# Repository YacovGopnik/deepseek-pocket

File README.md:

# DeepSeek в кармане

Самодельный карманный гаджет на ESP32-C3. Умеет:
- чат с DeepSeek;
- инженерный калькулятор с графиками и решением уравнений;
- справочник, конспекты, игры;
- общую «Комнату» для владельцев таких же устройств;
- игры вдвоём по радио;
- галерею на SD-карте;
- вывод картинок и экрана с компьютера;
- управление с телефона.

Обновляется по воздуху с этого репозитория.

## Что нужно

- ESP32-C3 Super Mini
- дисплей ST7789 240×240 1,3" (без вывода CS)
- аналоговый джойстик KY-023
- по желанию:
  - LiPo-аккумулятор и модуль зарядки с повышением до 5 В (USB-C), выключатель;
  - модуль microSD (например, V717) с конденсатором 100 мкФ;
  - пищалка, ИК-светодиод, белый светодиод (без SD-карты).

## Подключение

| Дисплей | ESP32-C3 |   | Джойстик | ESP32-C3 |
|---------|----------|---|----------|----------|
| SCL     | GPIO4    |   | VRx      | GPIO0    |
| SDA     | GPIO6    |   | VRy      | GPIO1    |
| DC      | GPIO5    |   | SW       | GPIO7    |
| RES     | GPIO21 (или GPIO3, см. ниже) | | +5V | **3V3** |
| BLK     | GPIO10   |   | GND      | GND      |
| VCC     | 3V3      |   |          |          |
| GND     | GND      |   |          |          |

### ESP32-S3 (S3-Zero)

Прошивка сама подставляет распиновку под плату: в Arduino IDE выберите **ESP32S3 Dev Module**, USB CDC On Boot: Enabled, Flash Size: 4MB, PSRAM: QSPI PSRAM, Partition Scheme: Minimal SPIFFS. По воздуху гаджет на S3 сам берёт сборки для S3 (`firmware-s3*.bin`).

| Что | S3-Zero |
|---|---|
| Экран SCL, SDA, DC, RES, BLK | 12, 11, 10, 9, 8 (VCC — 3V3) |
| Джойстик VRx, VRy, SW | 1, 2, 7 (питание — 3V3) |
| SD-карта SCK, MOSI, MISO, CS | 5, 6, 13, 4 (VCC — 5V; у карты своя шина SPI, подтяжки не нужны) |
| Батарея (делитель 100к + 100к) | 3 |
| Пищалка / ИК-светодиод | RX (44) / TX (43) |
| Усилитель MAX98357A: BCLK, LRC, DIN | 14, 15, 16 (VIN — 5V, SD и GAIN не подключать) |
| Микрофон INMP441: SCK, WS, SD | 14, 15, 17 (VDD — 3V3, L/R — GND) |
| Датчик наклона ADXL345: SDA, SCL | 38, 39 (VCC — 3V3, CS — 3V3, SDO — GND); Настройки → Наклон: уровень, калибровка, управление в играх |
| Фонарик / вибромотор | 18 / 40 |
| Не трогать | 0 (кнопка BOOT), 19–20 (USB), 21 (светодиод на плате), 45 (влияет на запуск) |

Выводы 14–18 и 38–40 у S3-Zero — площадки на плате. В нашем гаджете они выведены проводами на отдельную гребёнку. Порядок, если смотреть с гребёнкой вверх: **40, 39, 38, 18, 17, 14, 15, 16**.

### Сенсорные кнопки S3

В Настройки → Сенсорные кнопки доступны режимы 4 направления и 6 кнопок + BOOT. В режиме шести кнопок GPIO4/5/6/13 — вверх/вниз/влево/вправо, GPIO14 — OK, GPIO7 — ESC. Физический OK — кнопка BOOT платы. Перед включением режима отсоедините провод SW джойстика от GPIO7 и оборудование I²S от GPIO14. Цифровой звук I²S в этом режиме отключён. Для SD-карты необходимо выключить сенсорное управление. Режим меняется с перезапуском. На главном экране удерживайте BOOT, затем отпустите. В диалоге короткое нажатие BOOT включает режим «Только сенсоры» (аналоговые оси игнорируются), долгое выключает сенсоры. Не удерживайте BOOT при подаче питания или аппаратном сбросе.

### Батарея

- **RES экрана** можно подключить к GPIO21 (TX) или к GPIO3: прошивка подаёт сброс на оба вывода и сама понимает схему.
- **Проценты заряда.** RES подключите на GPIO21. Нужны два резистора по 100 кОм: один от «+» питания к GPIO3, второй от GPIO3 к GND. Прошивка сама находит делитель при включении.

### Выводы, которые делят SD-карта и дополнительные детали

GPIO2, GPIO8, GPIO9 и GPIO20 нужны либо SD-карте, либо пищалке, ИК-пульту и фонарику:

| Вывод | С SD-картой | Без SD-карты |
|---|---|---|
| GPIO8 | SCK карты | ИК-светодиод (через транзистор) |
| GPIO2 | MOSI карты | фонарик (через транзистор) |
| GPIO20 | MISO карты | пищалка |
| GPIO9 | CS карты | — |

Когда включена SD-карта, прошивка не трогает пищалку, ИК и фонарик. При попытке их включить она говорит, что вывод занят картой.

## Сборка в Arduino IDE

Проводом прошивать нужно один раз, дальше обновления приходят по воздуху.

1. На GitHub: **Code → Download ZIP**. Распакуйте архив («Извлечь всё»), не открывайте файлы прямо из ZIP.
2. Скетч лежит в папке **`deepseek_c3`**: откройте `deepseek_c3/deepseek_c3.ino`. В Arduino IDE должны появиться вкладки с остальными файлами (`admin.h`, `calc.h`...).
3. Пакет плат **esp32** (Espressif) 3.x. Библиотеки (Скетч → Подключить библиотеку → Управлять библиотеками):
   - **Adafruit ST7735 and ST7789**, **Adafruit GFX**, **ArduinoJson** (7.x), **TJpg_Decoder** (Bodmer);
   - для сборки с Bluetooth ещё **NimBLE-Arduino 1.4.3**.
4. Инструменты:
   - Плата **ESP32C3 Dev Module** с разметкой **Partition Scheme: Minimal SPIFFS (1.9MB APP with OTA/190KB SPIFFS)**.

     Другой вариант: плата **Nologo ESP32C3 Super Mini** с разметкой **Huge APP**. Так прошивка выйдет на 16 КБ меньше, и именно так собирает GitHub. Настоящую разметку в обоих случаях задаёт файл `partitions.csv` в папке скетча.
   - **USB CDC On Boot: Enabled** — обязательно. Иначе вывод в монитор порта идёт через GPIO21 и сбрасывает экран.
   - **Erase All Flash Before Sketch Upload: Disabled** — иначе каждая прошивка стирает сеть, ключ и файлы.
5. Загрузить. Версия, собранная в Arduino IDE, показывается как «1». Номера сборок с GitHub больше, поэтому гаджет предложит обновиться.

Если плата не появляется в списке портов: зажмите кнопку **BOOT**, подключите USB и отпустите кнопку. Загрузите прошивку, затем нажмите **RST**.

## Первый запуск

Гаджет создаёт сеть Wi-Fi **DeepSeek-Setup**. Подключитесь к ней с телефона: откроется страница, где вводятся сеть Wi-Fi и ключ DeepSeek (получить его можно на platform.deepseek.com). Ключи и пароли хранятся только в памяти платы, в файлах прошивки их нет.

## Главный экран

После включения открывается главный экран, как у телефона:
- **Сверху** строка состояния: время, Wi-Fi, заряд, новые сообщения комнаты.
- **Ниже** иконки приложений 3×3 на нескольких страницах.

Ручкой выбирается иконка. Если упереться в край, открывается соседняя страница. Нажатие открывает приложение, удержание кнопки возвращает назад.

Приложения: DeepSeek, Комната, Игры, Калькулятор, Справочник, Конспекты, Сохранено, Википедия, Картинки, Галерея, Погода, Курсы, Часы, Таймер, Секундомер, Пульт (ИК), Bluetooth, Экран ПК, Телефон, Настройки, Админ.

**Если гаджет завис** — держите кнопку джойстика 6 секунд: он перезапустится и откроет главный экран. Это срабатывает, даже если программа намертво застряла (например, на SD-карте). Через 2 секунды экран гаснет, держите дальше.

Что настраивается:
- **Ось Y джойстика** — если вверх и вниз на ручке перепутаны.
- **Поворот экрана** — поворачивает картинку на 90° за нажатие, например чтобы держать гаджет боком. Ручка поворачивается вместе с картинкой.
- **Джойстик** — чувствительность: 1 — отклонять до упора, 5 — хватает лёгкого наклона.

## Возможности

- **Чат с DeepSeek.** Помнит переписку, ответ печатается по мере генерации. Есть «решить по шагам» и «объяснить проще». Удержание кнопки на клавиатуре чата открывает меню: новый чат, шаблоны вопросов, сохранённое.
- **Языки:** русский, английский, китайский. Экранная клавиатура с подсказками слов.
- **Тексты без интернета:** шаблоны вопросов, сохранённые ответы и конспекты.
- **Справочник:** формулы, константы, таблица Менделеева.
- **Калькулятор** с переменной x, графиками и уравнениями (см. ниже).
- **Интернет:** Википедия, картинки (Wikimedia Commons), погода, курсы ЦБ.
- **Время:** часы, таймер, секундомер.
- **Галерея:** картинки с телефона, с компьютера или из поиска. Без SD-карты хранится до 30 штук, с картой до 99.
- **Игры:**
  - шахматы против DeepSeek или самой платы;
  - «Подземелье 3D» — стрелялка от первого лица: ручка — идти и поворачивать, кнопка — выстрел;
  - «Песочница» — двумерный мир из блоков: копать, строить, мастерить кирки и мечи, ночью отбиваться от слизней; цель — золотая корона (см. ниже);
  - «Гонки», «Райдер», «Блоки», 2048, «Змейка», «Падающие блоки», «Лабиринт», «Память», «Пинг-понг», «Летящая птичка», «Арканоид», «Пришельцы», «Сапёр», «Повтори»;
  - «Куб-раннер» — уровень с финишем, шипами и платформами. Короткое нажатие кнопки или наклон джойстика вверх запускает забег, прыжок и повтор попытки. Удержание кнопки возвращает в меню. Прогресс и рекорд показываются в процентах.
  - игры с DeepSeek: «Викторина», «Приключение», «Угадай, кто я»;
  - общая таблица рекордов;
  - крестики-нолики через комнату и «Крестики рядом» по радио.
- **Пульт (ИК)** — пульты из базы Flipper-IRDB. Скачиваются с GitHub прямо с гаджета или загружаются файлом .ir с телефона. Только без SD-карты. Схема: GPIO8 → база NPN-транзистора (S9014), коллектор → 5V, эмиттер → «+» ИК-светодиода, «−» светодиода → резистор 33–68 Ом → GND.
- **Фонарик:** Настройки → Фонарик. Белый светодиод на GPIO2 через транзистор, схема в начале скетча рядом с `PIN_LED`. Только без SD-карты.
- **Пищалка** на GPIO20. Для активной пищалки в скетче поставьте `BUZZER_ACTIVE = true`. Звук настраивается: нет / сигналы / всё.
- **Wi-Fi и экран:** до 5 сетей Wi-Fi, автогашение экрана, заставка с часами.

## Телефон как пульт и клавиатура (Wi-Fi)

Приложение **«Телефон»** показывает адрес гаджета, например `http://192.168.1.35`. Подключите телефон к той же сети Wi-Fi и откройте этот адрес в любом браузере (Android или iPhone). Ничего устанавливать не нужно: гаджет сам отдаёт страницу.

На странице:
- **Стрелки.** Пока стрелку держат, это как наклон ручки.
- **OK.** Это как нажатие ручки. Если держать дольше полсекунды, получится долгое нажатие.
- **Поле для текста** с кнопками «Отправить» (вставить и нажать OK) и «Только вставить».

Пульт работает везде, где есть Wi-Fi: в играх, меню и при вводе текста. Из приложения «Телефон» можно выйти. Если связь пропала, нажатые кнопки отпускаются сами. Пульт есть только в полной сборке.

## Экран ПК (USB)

Приложение **«Экран ПК»** показывает на гаджете картинки и экран компьютера по USB-кабелю. На компьютере откройте в Chrome или Edge страницу [yacovgopnik.github.io/deepseek-pocket/pc.html](https://yacovgopnik.github.io/deepseek-pocket/pc.html), нажмите «Подключить» и выберите порт гаджета. Для передачи с ПК выберите «ПК → гаджет» в меню приложения. Монитор порта в Arduino IDE при этом должен быть закрыт.

- **Картинка.** Перетащите файл или вставьте через Ctrl+V, затем «Показать на гаджете» или «Сохранить в галерею».
- **Трансляция экрана.** Гаджет показывает выбранное окно, вкладку или весь экран, от 2 до 20 кадров в секунду.

- **Экран гаджета на ПК.** Выберите «Гаджет → ПК» на гаджете, вернитесь в меню и нажмите «Экран гаджета» на странице. Можно увеличивать изображение, открывать его на весь экран и сохранять PNG. На S3 изображение 240×240, на C3 — 120×120 для экономии памяти. Для остановки на гаджете снова откройте «Экран ПК» и выберите остановку трансляции. Доступно в полной сборке.

Как устроен обмен: страница сжимает кадр в JPEG 240×240 и передаёт его кусками по 2 КБ, гаджет подтверждает каждый кусок. Все подробности протокола — в начале раздела «ЭКРАН ПК» в скетче.

## Игры вдвоём рядом (без интернета)

**Игры → Крестики рядом** — два гаджета связываются напрямую по радио (ESP-NOW), без роутера и интернета, на расстоянии примерно до 100 м. На время игры Wi-Fi отключается от сети, а после игры подключается снова.

## SD-карта

| SD-модуль | ESP32-C3 |
|---|---|
| SCK | GPIO8 |
| MOSI | GPIO2 |
| MISO | GPIO20 |
| CS | GPIO9 |
| VCC | **5V** (у модуля свой стабилизатор 3,3 В; от 3V3 ему не хватает) |
| GND | GND, отдельным проводом к плате |

- **Конденсатор 100 мкФ** (можно вместе с керамическим 0,1 мкФ) ставится прямо на выводы VCC–GND модуля. Без него карта отвечает через раз: в момент обращения к ней проседает питание.
- **Два резистора по 10 кОм:** от GPIO2 к 3V3 и от GPIO9 к 3V3. При включении эти выводы должны быть в высоком уровне, иначе плата не загрузится.
- **Карта** до 32 ГБ, формат FAT32.

Включение: **Настройки → SD-карта**, гаджет перезапустится. Состояние видно там же: «работает», «не найдена» или «сбой N». После включения:
- галерея хранится на карте (папка `pics/`, до 99 картинок);
- в меню **Настройки → Обновление** появляется пункт **«Сборки на SD-карте»**: скачать обе сборки на карту (папка `fw/`) и переключаться между ними без интернета.

Заметки, сохранённые ответы и настройки остаются во внутренней памяти.

Если сразу после включения карта не отвечает, гаджет пробует снова каждые 15 секунд в течение 2 минут.

**Защита от зависания.** Если запуск с картой не дошёл до конца, на следующем запуске карта выключается сама, а на заставке видно, на каком шаге всё остановилось. Удержание кнопки при включении тоже выключает карту.

**Как устроено.** Шина SPI у платы одна, а у экрана нет вывода CS. Поэтому на время работы с картой выводы шины переключаются на неё, а потом обратно на экран. При переключении линия такта не дёргается: иначе экран без CS сбивается и перестаёт понимать команды.

**Проверка.** В папке [`tests`](tests) лежат отдельные скетчи:
- `sd_diag` проверяет карту медленно, быстро и вместе с экраном и пишет, в чём беда: питание и провода, длинные провода или прошивка;
- `sd_screen_test` по кругу переключается между картой и экраном.

## Песочница

**Игры → Песочница.** Мир 256×96 блоков создаётся заново для каждой новой игры: холмы, деревья, пещеры, уголь, железо, золото у самого дна. День длится 5 минут, ночь 3 минуты. Под землёй темно, и нужны факелы.

- **Управление.**
  - Ручка влево/вправо — идти, вверх — прыжок. Куда наклонена ручка, туда и цель (белая рамка).
  - Нажатие — ударить по блоку, поставить выбранный блок в пустое место или ударить слизня.
  - Удержание кнопки — меню: что ставить, мастерить, сохранить и выйти.
- **Инструменты** работают сами, пока лежат в рюкзаке: самая лучшая кирка копает, самый лучший меч бьёт. Без кирки копаются только земля, песок и дерево. Деревянная кирка берёт камень и уголь, каменная — железо, железная — золото.
- **Рецепты:**
  - доски — из брёвен;
  - верстак — из досок;
  - факелы — из угля или слизи с досками;
  - у верстака: кирки, мечи, кирпич и золотая корона.
- **Сохранение.** Мир весит около 25 КБ и хранится на SD-карте, а без неё — во внутренней памяти. Он сохраняется сам каждые 3 минуты, а также через меню «Сохранить и выйти».

## Три сборки: полная, с Bluetooth и игровая

Bluetooth весит около 250 КБ, и всё вместе в память на 4 МБ не помещается. Поэтому GitHub собирает три прошивки:

- **Полная сборка** (`firmware.bin`): всё, кроме Bluetooth.
- **Сборка с Bluetooth** (`firmware-ble.bin`): связь с телефоном по Bluetooth и пульт для музыки на телефоне. В ней **нет**:
  - картинок из интернета (галерея остаётся);
  - шахмат;
  - «Подземелья 3D» и «Гонок»;
  - «Райдера», «Викторины», «Приключения»;
  - ИК-пульта и фонарика;
  - пульта с телефона по Wi-Fi;
  - «Песочницы».
- **Игровая сборка** (`firmware-games.bin`): только игры (в том числе большие), «Комната», пульт с телефона и настройки. Здесь остаётся больше места под новые большие игры. Чата DeepSeek, справочника, калькулятора и остальных приложений в ней нет. Игры с DeepSeek работают, если задан ключ.

Переключение: **Настройки → Обновление → Сменить сборку** или **Сборки на SD-карте** (туда скачиваются все три). Настройки, сети и файлы сохраняются. Для сборки в Arduino IDE поставьте в начале скетча `#define ENABLE_BLE 1` (с Bluetooth) или `#define GAMES_EDITION 1` (игровая).

В сборке с Bluetooth включите **Настройки → Bluetooth**. Гаджет называется **DS-<метка>**.

- **Телефон как клавиатура и уведомления.**
  - Откройте в Chrome на Android страницу [yacovgopnik.github.io/deepseek-pocket/ble.html](https://yacovgopnik.github.io/deepseek-pocket/ble.html) и нажмите «Подключить». Подойдёт и приложение Serial Bluetooth Terminal в режиме Bluetooth LE.
  - Текст попадает в открытое поле ввода, например как вопрос DeepSeek. Если поле ввода не открыто, текст всплывает как уведомление.
  - Строка с `N:` в начале — всегда уведомление, с `T:` — только вставить.
- **Пульт для телефона.** На телефоне в настройках Bluetooth подключитесь к **DS-<метка>**. На гаджете откройте приложение Bluetooth → Пульт. Ручка влево и вправо переключает трек, вверх и вниз меняет громкость, нажатие ставит на паузу.

Wi-Fi и Bluetooth делят память. Если запросы в интернет начнут срываться, выключите Bluetooth.

## Страницы для телефона и компьютера

Страницы `ble.html` и `pc.html` лежат в корне репозитория. Их адреса `yacovgopnik.github.io/...` работают, когда в репозитории включён GitHub Pages: **Settings → Pages → Branch: main, папка / (root)**. Страница `room.html` открывает «Комнату» в браузере.

## Администратор

Один человек может быть администратором всех гаджетов с этой прошивкой. Команды подписываются ключом, который получается из логина и пароля админа (ECDSA P-256). В прошивке хранится только открытый ключ `ADMIN_PUBKEY`, по которому гаджеты проверяют подпись. Подделать команду без пароля нельзя, даже зная исходный код. Пароль нигде не записывается.

Как стать админом:

1. **Настройки → Администратор → Создать ключ**: ввести логин и пароль. Открытый ключ появится на экране и в мониторе порта (115200).
2. Вписать его в `ADMIN_PUBKEY` в начале скетча и выпустить новую версию.
3. **Настройки → Администратор → Войти** с теми же логином и паролем. Вход действует до перезапуска. На главном экране появляется приложение «Админ».

Что может админ:

- **Гаджеты на связи**: имя, комната, версия прошивки, заряд. Для каждого гаджета: обновить прошивку, перезапустить, выгнать из комнаты, заблокировать.
- **Объявление всем**: всплывает на экране всех гаджетов, в том числе тех, кто подключится позже.
- **Сообщения комнаты**: удалить сообщение у всех, заблокировать автора. Заблокированный не может писать, а его сообщения у других не показываются.
- **Закрепить в комнате**: строка сверху экрана комнаты.
- **Обновить все гаджеты / перезапустить все**.

Владелец гаджета видит каждое действие админа. Обновление и перезапуск начинаются через 10 секунд, и их можно отменить кнопкой.

Команды идут через тот же открытый сервер, что и «Комната». Поэтому их получают только гаджеты, у которых в комнате задано имя и включены «Сообщения в фоне». Старые и повторённые команды не принимаются: нужно точное время, гаджет берёт его из интернета.

## Калькулятор: функции, графики, уравнения

Клавиша **2nd** переключает на вторую страницу клавиш, **1st** возвращает обратно. Переменная **x** есть на обеих страницах.

- **Функции.** Вводите выражение с x: `2x²-3x+1`, `sin(x)/x`, `√x`, `3x^4`. Неявное умножение работает (`2x`, `3(x+1)`). Результата у такого выражения нет, калькулятор пишет «функция f(x)».
- **График y(x)** (2nd → `y(x)`):
  - вверх/вниз — масштаб, влево/вправо — сдвиг;
  - нажатие — курсор со значениями x и y, удержание — назад;
  - масштаб по y подбирается сам;
  - если выражение пустое, строится последняя функция;
  - для sin/cos/tan в градусах окно по умолчанию шире (720°).
- **Уравнения** (2nd → `x=?`). Знак равенства вводится клавишей `L=R`: `x²=x+2`, `3x^4=48`. Без знака равенства считается «выражение = 0».
  - Многочлены и одночлены до 8-й степени решаются точно: рациональные корни находятся целиком, показывается кратность корней, комплексные корни выводятся как `a ± bi`.
  - Остальные уравнения (`sin(x)=0,5`, `1/x=2`, `√x=2`) решаются приближённо: ищется смена знака на отрезке. Отрезок: [-100; 100], для тригонометрии в градусах [-720; 720], в радианах [-20; 20]. Корни, в которых график лишь касается оси, так не находятся.

## Комната

Гаджеты с этой прошивкой встречаются в общей комнате `lobby` на открытом MQTT-сервере `broker.emqx.io`.

- **Сообщения** идут в теме `dspocket/v1/<комната>` в виде `метка<TAB>имя<TAB>текст`.
- **Присутствие** («кто в комнате») — в теме `<комната>/p`.
- **Аватарки 24×24** — в теме `<комната>/a/<метка>`: 576 байт, сохраняемое сообщение.
- **Ответ DeepSeek:** сообщение, начатое с `@ai`, получает ответ, который видят все.

В комнату можно зайти и из браузера через страницу `room.html`.

Сообщения **не шифруются** и не хранятся: их видят все, кто сейчас в комнате. Не пишите туда пароли и личные данные. Сервер и комнату по умолчанию можно поменять в начале скетча (`MQTT_HOST`, `ROOM_DEFAULT`).

## Обновление по воздуху

На гаджете: **Настройки → Обновление**. Там есть «Проверить в интернете», «С телефона» (загрузить файл `.bin` через страницу гаджета) и «Сборки на SD-карте». Если обновление оборвалось, остаётся старая прошивка.

Новые версии собираются сами. При каждом изменении кода GitHub Actions собирает все три сборки и кладёт в папку `firmware/`:
- `firmware/firmware.bin` — полная сборка;
- `firmware/firmware-ble.bin` — сборка с Bluetooth;
- `firmware/firmware-games.bin` — игровая сборка;
- `firmware/version.txt` — номер версии.

Гаджет сравнивает этот номер со своим и предлагает обновиться. Репозиторий задаётся строкой `OTA_REPO` в начале скетча.

Китайский язык выключен (`ENABLE_CJK 0` в начале скетча), иначе прошивка не помещается в разметку с обновлением по воздуху.

## Плата

Черновик печатной платы-основы лежит в папке [`hardware`](hardware/README.md). Он сделан до SD-карты и модуля зарядки с USB-C, поэтому будет переделан под настоящие размеры модулей.

## Шрифты

Латиница, кириллица и знаки формул сделаны из DejaVu Sans Mono, иероглифы — из GNU Unifont и Noto Sans CJK. У этих шрифтов свои свободные лицензии.

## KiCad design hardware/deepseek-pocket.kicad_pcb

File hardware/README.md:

# Плата-основа (KiCad)

> **Черновик, будет переделан.** Плата сделана до SD-карты и до модуля зарядки с USB-C и повышением до 5 В. Сейчас в гаджете стоят они, а пищалка, ИК и фонарик сняты: их выводы GPIO2, GPIO8 и GPIO20 заняты картой (подключение — в главном [README](../README.md#sd-карта)). Новая плата будет сделана по замерам настоящих модулей. В неё войдут гнездо microSD, конденсатор 100 мкФ у карты и подтяжки GPIO2 и GPIO9 к 3V3. Не заказывайте эту версию.

Двусторонняя плата 61 × 102 мм. На неё впаиваются готовые модули: ESP32-C3 Super Mini, экран, джойстик, зарядка TP4056. На самой плате стоят питание с выключателем, делитель для процентов заряда, пищалка, ИК-светодиод для «Пульта» и фонарик. Все подключения совпадают с прошивкой, менять в ней ничего не нужно.

На картинке красным показаны дорожки сверху, синим снизу. Нижняя сторона дополнительно заливается землёй (GND), на картинке заливки нет.

## Файлы

- `deepseek-pocket.kicad_pro`, `deepseek-pocket.kicad_pcb` — проект для KiCad 8 или новее.
- `gen_pcb.py` — скрипт, который создал плату: размещение, трассировку и проверку зазоров. Изменили размещение — запустите `python3 gen_pcb.py`, и плата пересоберётся.
- Отдельной принципиальной схемы нет, соединения перечислены ниже.

## Соединения

| Что | Куда |
|---|---|
| Экран J1: GND, VCC, SCL, SDA, RES, DC, BLK | GND, 3V3, GPIO4, GPIO6, GPIO21, GPIO5, GPIO10 |
| Джойстик J2: GND, +5V, VRx, VRy, SW | GND, **3V3**, GPIO0, GPIO1, GPIO7 |
| Аккумулятор J3 (+, −) | B+, B− модуля TP4056 (J4) |
| TP4056 J4: OUT+ | выключатель SW1 → диод D1 → вывод 5V модуля |
| TP4056 J4: OUT− | GND |
| Делитель R1, R2 (100k + 100k) | после выключателя → GPIO3 → GND |
| Пищалка BZ1 | «+» на GPIO20, «−» на GND |
| ИК: Q1 S9014 | база — GPIO8, коллектор — 5V, эмиттер → ИК-светодиод D2 → R3 47 Ом → GND |
| Фонарик: Q2 S9014 | GPIO2 → R4 22k → база; R6 4,7k с GPIO2 на 3V3; 5V → R5 47 Ом → светодиод D3 → коллектор; эмиттер — GND |

## Что купить

| Обозначение | Деталь | Шт. |
|---|---|---|
| U1 | ESP32-C3 Super Mini + 2 гребёнки по 8 штырей | 1 |
| J1 | экран ST7789 240×240 1,3" (7 выводов, без CS) + гнездо 1×7 | 1 |
| J2 | джойстик KY-023 + провода или гнездо 1×5 | 1 |
| J4 | модуль TP4056 **с защитой** (6 площадок: B+ B− OUT+ OUT−) | 1 |
| J3 | аккумулятор LiPo 3,7 В (например, 500–1000 мА·ч) | 1 |
| SW1 | движковый выключатель (SS12D00 или любой, на проводах) | 1 |
| D1 | диод Шоттки 1N5819 | 1 |
| R1, R2 | резистор 100 кОм 0,25 Вт | 2 |
| R3, R5 | резистор 47 Ом 0,25 Вт | 2 |
| R4 | резистор 22 кОм | 1 |
| R6 | резистор 4,7 кОм | 1 |
| Q1, Q2 | транзистор S9014 (NPN, TO-92) | 2 |
| D2 | ИК-светодиод 5 мм, 940 нм | 1 |
| D3 | белый светодиод 5 мм | 1 |
| BZ1 | пищалка 12 мм, шаг выводов 7,6 мм (пассивная; для активной в скетче `BUZZER_ACTIVE = true`) | 1 |
| — | стойки и винты M3 | 4 |

## Перед заказом — обязательно

Плату я делал без KiCad, скриптом. Скрипт сам проверяет зазоры и что все сети соединены (0 ошибок), но окончательную проверку делает KiCad:

1. Откройте `deepseek-pocket.kicad_pro` в KiCad 8 или новее, затем «Редактор печатных плат».
2. Нажмите **B**: KiCad зальёт землю на нижней стороне.
3. **Инспектор → Проверка правил проектирования (DRC) → Запустить**. Ошибок быть не должно. Предупреждения о подписях и шелкографии не страшны.
4. **Проверьте модули по размерам.** Это самое важное: расстояние между рядами Super Mini (15,24 мм) и порядок его выводов взяты из типовой распиновки. Распечатайте плату 1:1 (**Файл → Печать**, масштаб 1:1, слои F.Cu и F.SilkS), положите модули на бумагу и сверьте: подписи 5V, G, 3.3, 4… на плате должны совпасть с подписями на вашем модуле. То же для экрана и TP4056.

## Заказ

1. В KiCad: **Файл → Выходные файлы для производства → Gerber**. Включите слои F.Cu, B.Cu, F.Mask, B.Mask, F.SilkS, B.SilkS, Edge.Cuts и нажмите «Создать файлы сверловки» (Excellon). Все файлы упакуйте в один ZIP.
2. Загрузите ZIP на сайт производителя печатных плат (JLCPCB, PCBWay, в России — например, Резонит). Сайт сам покажет плату.
3. Параметры: 2 слоя, 1,6 мм, любой цвет маски. Минимальные зазоры и дорожки на плате 0,2 мм и шире, отверстия от 0,4 мм — подходит самый дешёвый вариант.

## Сборка

- **Super Mini** впаивайте на штыревые гребёнки, а не вплотную: под модулем проходят дорожки и переходные отверстия. USB-разъём смотрит к нижнему краю.
- **Экран** ставится на высокое гнездо 1×7 (около 11 мм): под ним стоят резисторы и диод.
- **Светодиоды** D2 и D3 стоят у верхнего края: выведите их ножки так, чтобы светодиоды смотрели наружу. Длинная ножка (+) вставляется в отверстие с плюсом.
- **Транзисторы** ставятся плоской стороной к подписям E B C.
- **D1 или JP1 — только одно из двух.** Диод D1 защищает аккумулятор, когда гаджет подключён к компьютеру по USB модуля. Перемычка JP1 (кусок провода) вместо диода даёт на 0,3 В больше напряжения, но тогда **нельзя** подключать USB Super Mini при включённом выключателе.
- **Заряжать** через разъём модуля TP4056.

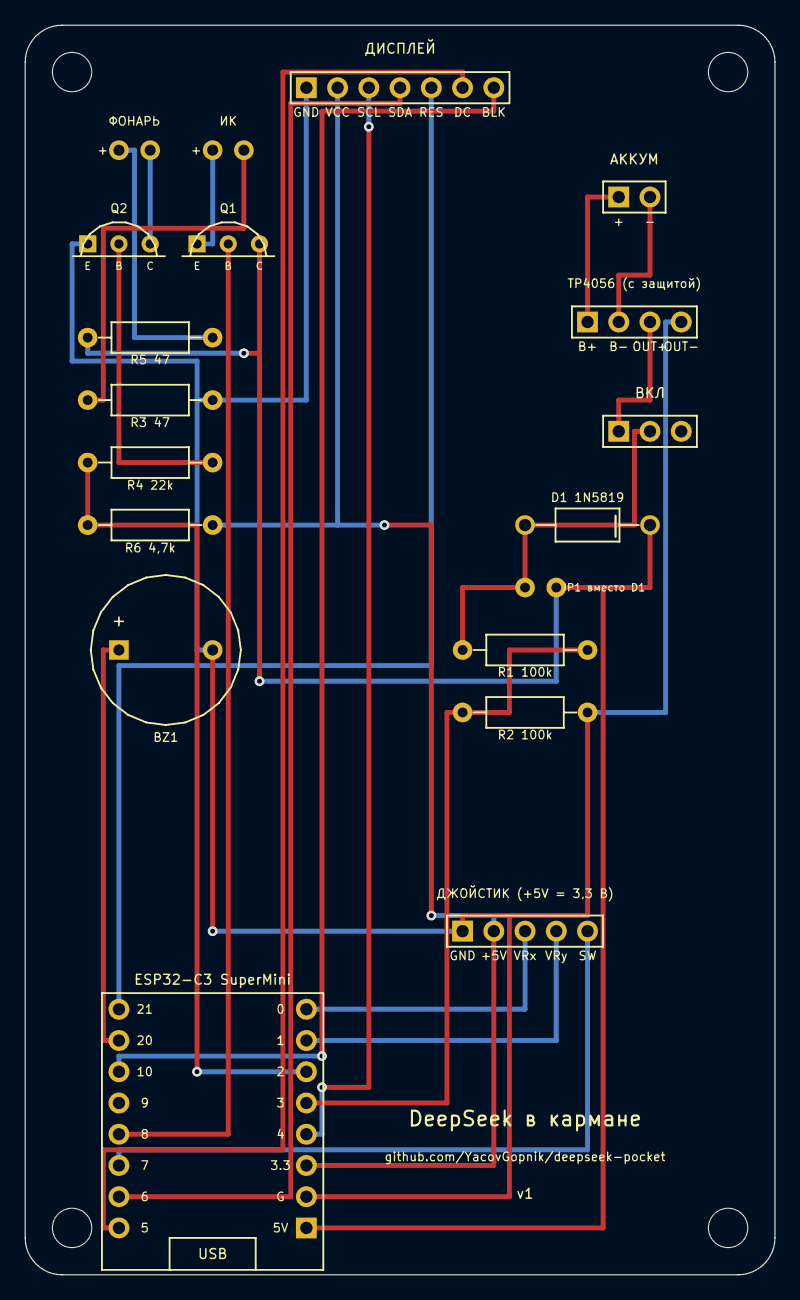
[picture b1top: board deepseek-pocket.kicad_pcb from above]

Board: 2 copper layers, 61.0 x 101.6 mm, 20 parts (0 on the bottom side), 24 nets.

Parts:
BZ1: Пищалка 12мм; BZ1
D1: 1N5819; D1
D2: ИК-светодиод 5мм 940нм; D2
D3: LED белый 5мм; D3
H1: M3; H1
J1: Дисплей ST7789; J1
J2: Джойстик KY-023; J2
J3: Аккумулятор; J3
J4: TP4056; J4
JP1: Перемычка; JP1
Q1: S9014; Q1
Q2: S9014; Q2
R1: 100k; R1
R2: 100k; R2
R3: 47; R3
R4: 22k; R4
R5: 47; R5
R6: 4.7k; R6
SW1: Выключатель; SW1
U1: ESP32-C3 Super Mini; U1

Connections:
+3V3: J1.2, J2.2, R6.2, U1.R3
+5V: D1.2, JP1.2, Q1.3, R5.1, U1.R1
BATN: J3.2, J4.2
BATP: J3.1, J4.1
BATS: R1.2, R2.1, U1.R5
BLK: J1.7, U1.L6
BUZ: BZ1.1, U1.L7
DC: J1.6, U1.L1
GND: BZ1.2, J1.1, J2.1, J4.4, Q2.1, R2.2, R3.2, U1.R2
IR: Q1.2, U1.L4
IRA: D2.1, Q1.1
IRK: D2.2, R3.1
JSW: J2.5, U1.L3
JX: J2.3, U1.R8
JY: J2.4, U1.R7
LED: R4.1, R6.1, U1.R6
LEDA: D3.1, R5.2
LEDB: Q2.2, R4.2
LEDK: D3.2, Q2.3
MOSI: J1.4, U1.L2
RES: J1.5, U1.L8
SCK: J1.3, U1.R4
VOUT: J4.3, SW1.1
VSW: D1.1, JP1.1, R1.1, SW1.2

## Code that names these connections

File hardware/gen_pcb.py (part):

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
# ---- разъёмы модулей ----
header_row("J1", "Дисплей ST7789", 22.86, 5.08, ["GND", "+3V3", "SCK", "MOSI", "RES", "DC", "BLK"],
           ["GND", "VCC", "SCL", "SDA", "RES", "DC", "BLK"], label_side=2.0)
parts[-1].texts.append(("ДИСПЛЕЙ", 30.48, 1.9, 0.8))
header_row("J2", "Джойстик KY-023", 35.56, 73.66, ["GND", "+3V3", "JX", "JY", "JSW"],
           ["GND", "+5V", "VRx", "VRy", "SW"], label_side=2.0)
parts[-1].texts.append(("ДЖОЙСТИК (+5V = 3,3 В)", 40.64, 70.6, 0.7))
header_row("J3", "Аккумулятор", 48.26, 13.97, ["BATP", "BATN"], ["+", "-"], label_side=2.0)
parts[-1].texts.append(("АККУМ", 49.53, 10.9, 0.8))
header_row("J4", "TP4056", 45.72, 24.13, ["BATP", "BATN", "VOUT", "GND"], ["B+", "B-", "OUT+", "OUT-"], label_side=2.0)
parts[-1].texts.append(("TP4056 (с защитой)", 49.53, 21.0, 0.7))
header_row("SW1", "Выключатель", 48.26, 33.02, ["VOUT", "VSW", None], ["", "", ""], label_side=2.0)
parts[-1].texts.append(("ВКЛ", 50.8, 29.9, 0.8))

# ---- питание ----
two_pin("D1", "1N5819", 40.64, 40.64, 50.8, 40.64, "VSW", "+5V", drill=1.0, l1=None, body=(5.2, 2.7))
parts[-1].texts += [("D1 1N5819", 45.72, 38.4, 0.7), ("|", 48.0, 40.64, 1.2)]
two_pin("JP1", "Перемычка", 40.64, 45.72, 43.18, 45.72, "VSW", "+5V", drill=0.8)
parts[-1].texts.append(("JP1 вместо D1", 47.0, 45.72, 0.6))
two_pin("R1", "100k", 35.56, 50.8, 45.72, 50.8, "VSW", "BATS", body=(6.3, 2.5))
parts[-1].texts.append(("R1 100k", 40.64, 52.6, 0.7))
two_pin("R2", "100k", 35.56, 55.88, 45.72, 55.88, "BATS", "GND", body=(6.3, 2.5))
parts[-1].texts.append(("R2 100k", 40.64, 57.7, 0.7))

# ---- фонарик и ИК (светодиоды у верхнего края - выгнуть наружу) ----
two_pin("D3", "LED белый 5мм", 7.62, 10.16, 10.16, 10.16, "LEDA", "LEDK", drill=0.9)
parts[-1].texts.append(("ФОНАРЬ", 8.89, 7.8, 0.7))
parts[-1].texts.append(("+", 6.3, 10.16, 0.7))
two_pin("D2", "ИК-светодиод 5мм 940нм", 15.24, 10.16, 17.78, 10.16, "IRA", "IRK", drill=0.9)
parts[-1].texts.append(("ИК", 16.51, 7.8, 0.7))
parts[-1].texts.append(("+", 13.9, 10.16, 0.7))
to92("Q2", "S9014", 5.08, 17.78, "GND", "LEDB", "LEDK")
parts[-1].texts.append(("Q2", 7.62, 14.9, 0.7))
to92("Q1", "S9014", 13.97, 17.78, "IRA", "IR", "+5V")
parts[-1].texts.append(("Q1", 16.51, 14.9, 0.7))
two_pin("R5", "47", 5.08, 25.4, 15.24, 25.4, "+5V", "LEDA", body=(6.3, 2.5))
parts[-1].texts.append(("R5 47", 10.16, 27.2, 0.7))
two_pin("R3", "47", 5.08, 30.48, 15.24, 30.48, "IRK", "GND", body=(6.3, 2.5))
parts[-1].texts.append(("R3 47", 10.16, 32.3, 0.7))
two_pin("R4", "22k", 5.08, 35.56, 15.24, 35.56, "LED", "LEDB", body=(6.3, 2.5))
parts[-1].texts.append(("R4 22k", 10.16, 37.4, 0.7))
two_pin("R6", "4.7k", 5.08, 40.64, 15.24, 40.64, "LED", "+3V3", body=(6.3, 2.5))
parts[-1].texts.append(("R6 4,7k", 10.16, 42.5, 0.7))

# ---- пищалка 12 мм, шаг 7,62 ----
bz = two_pin("BZ1", "Пищалка 12мм", 7.62, 50.8, 15.24, 50.8, "BUZ", "GND", drill=0.9, l1="+")
bz.texts.append(("+", 7.62, 48.4, 0.9))
bz.texts.append(("BZ1", 11.43, 57.9, 0.7))
for k in range(24):
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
